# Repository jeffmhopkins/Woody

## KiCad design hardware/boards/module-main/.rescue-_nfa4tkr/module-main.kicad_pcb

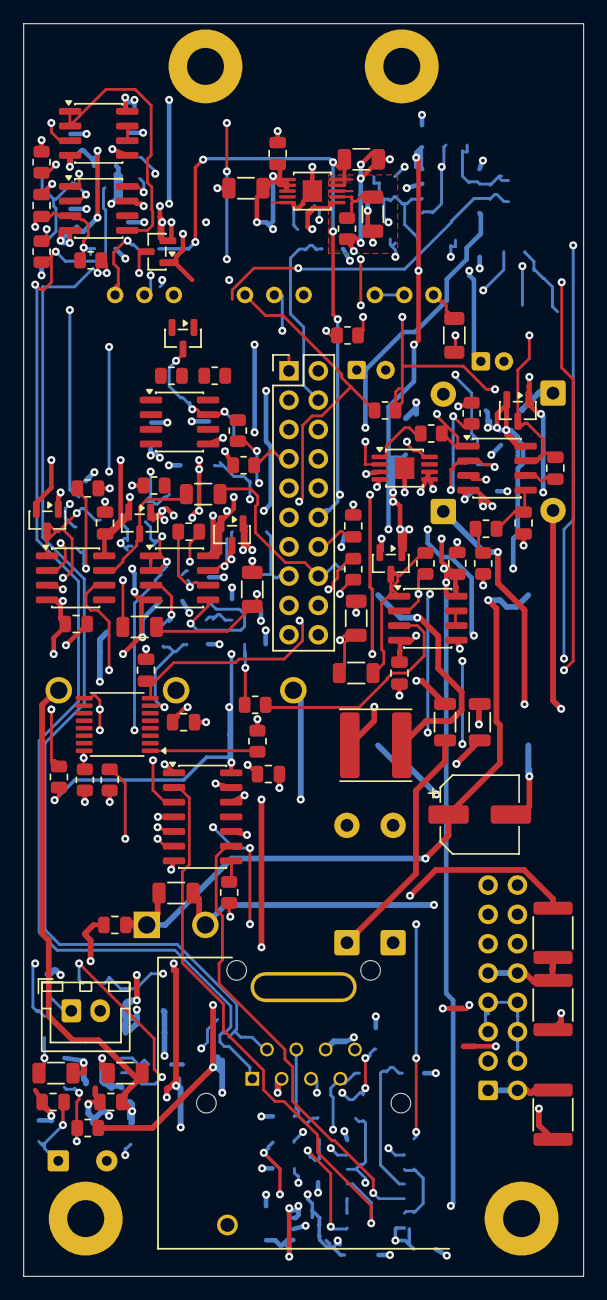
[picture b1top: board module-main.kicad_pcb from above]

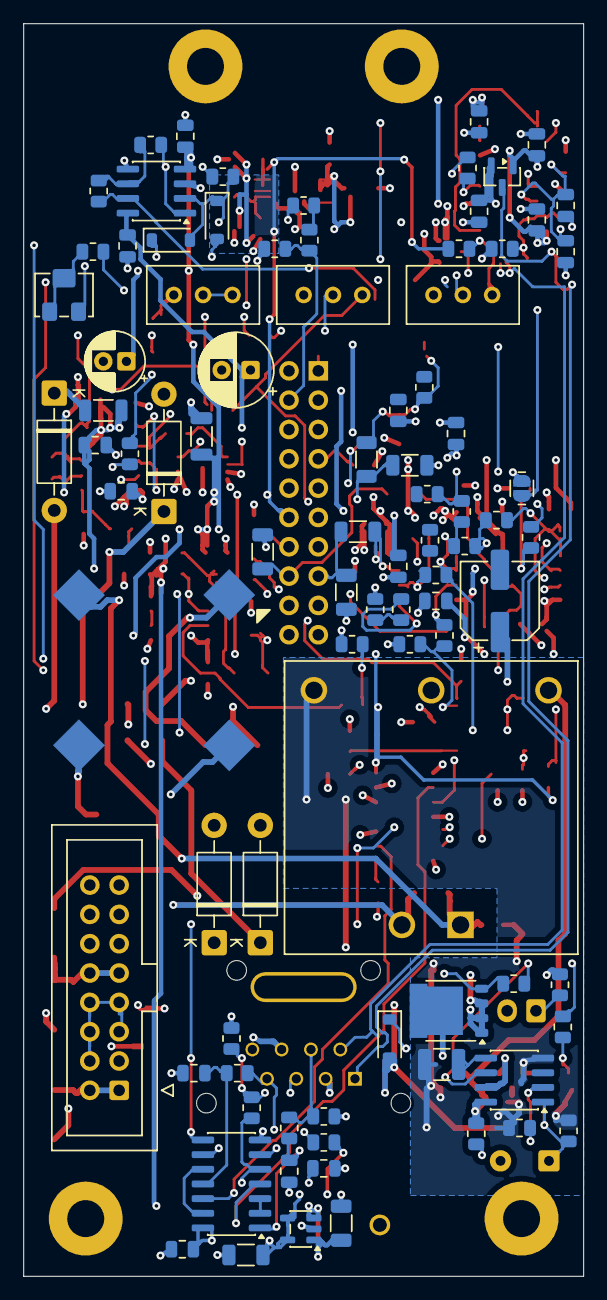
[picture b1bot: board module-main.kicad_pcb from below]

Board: 4 copper layers, 48.5 x 108.5 mm, 177 parts (89 on the bottom side), 113 nets.

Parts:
C1: 100uF; CP_Radial_D6.3mm_P2.50mm
C2: 100uF 50V; CP_Elec_6.3x7.7
C3: 47uF; CP_Radial_D5.0mm_P2.00mm
C5: 100nF; C_1206_3216Metric
C6, C51: 10uF; C_1206_3216Metric
C7, C10, C11, C12, C16, C17, C18, C19, C20, C21, C23, C24, C25, C26, C30, C31, C32, C33, C34, C35, C40, C43, C50: 100nF; C_0805_2012Metric
C8, C36, C37, C38, C39: 82nF; C_1206_3216Metric
C9: 10uF; C_1210_3225Metric
C13, C14: 1.5nF; C_0805_2012Metric
C15: 15nF; C_0805_2012Metric
C22: 330nF film; C_1206_3216Metric
C27, C29: 10nF; C_0805_2012Metric
C28: 2.2nF; C_0805_2012Metric
C41, C42: 4.7uF; C_1206_3216Metric
C44: 4.7uF 50V; C_1206_3216Metric
C45: 100uF 25V; CP_Elec_6.3x5.8
C46: 22nF; C_0805_2012Metric
C47, C48, C49: 47pF C0G; C_0805_2012Metric
D1, D2, D3, D15: 1N5817; D_DO-41_SOD81_P10.16mm_Horizontal
D4, D5, D6, D9, D10, D11, D12, D13: BAV99; SOT-23
D7, D8: 1N4448W; D_SOD-123
D14: 15V; D_SOD-123
F1, F3: MF-MSMF020/60-2; Fuse_1812_4532Metric
F2: MF-MSMF075/33X-2; Fuse_1812_4532Metric
FB1, FB2, FB3, FB4: 600R @ 100MHz; L_1206_3216Metric
H1: MECH-STANDOFF-MOD 1; MountingHole_3.2mm_M3_Pad
H2: MECH-STANDOFF-MOD 2; MountingHole_3.2mm_M3_Pad
H3: MECH-PANEL-STANDOFF-MOD 1; MountingHole_3.2mm_M3_Pad
H4: MECH-PANEL-STANDOFF-MOD 2; MountingHole_3.2mm_M3_Pad
J1: 2x8 2.54mm shrouded box header (16-pin); IDC-Header_2x08_P2.54mm_Vertical
J2: 2x10 2.54mm pin header; PinHeader_2x10_P2.54mm_Vertical
J3: Neutrik NE8FAV; Neutrik_NE8FAV_etherCON_Vertical
J4: JST B2B-XH-A; JST_XH_B2B-XH-A_1x02_P2.50mm_Vertical
JP1: 2-pad solder link; SolderJumper-2_P1.3mm_Open_RoundedPad1.0x1.5mm
L1: 22uH; L_Sunlord_SWPA6028S
L2: 1mH; L_CommonModeChoke_Bourns_PM3700
NT1, NT2, NT3: net tie; NetTie-2_SMD_Pad0.5mm
Q1: PSMN2R0-30YLE; LFPAK56
R1: 52.3k 0.1%; R_0805_2012Metric
R3: 50m 1% 1W; R_1206_3216Metric
R4: 10R 5%; R_0805_2012Metric
R5: 1k 5%; R_0805_2012Metric
R6: 35.7k 1%; R_0805_2012Metric
R7: 5.11k 1%; R_0805_2012Metric
R8, R10, R11, R13, R14, R15, R22, R28, R29, R30, R58, R59: 10k 1%; R_0805_2012Metric
R9: 0R strap; R_0805_2012Metric
R12, R33, R36, R38, R43, R48, R53: 100k 1%; R_0805_2012Metric
R16, R17, R39, R44, R49, R54, R65: 10k 0.1%; R_0805_2012Metric
R18, R19: 1M 1%; R_0805_2012Metric
R20: 42.2k 0.1%; R_0805_2012Metric
R21: 7.15k 1%; R_0805_2012Metric
R23: 21.0k 1%; R_0805_2012Metric
R24: 95.3k 1%; R_0805_2012Metric
R25: 40.2k 1%; R_0805_2012Metric
R26, R34, R41, R46, R51, R56: 1k 1%, >=500mW; R_1206_3216Metric
R27, R60: 20k 1%; R_0805_2012Metric
R31: 2.7k 1%; R_0805_2012Metric
R32, R35, R37, R42, R47, R52, R68, R69, R70: 1k 1%; R_0805_2012Metric
R40, R45, R50, R55: 30k 0.1%; R_0805_2012Metric
R57: 68k 1%; R_0805_2012Metric
R61: 100R 0.1%; R_0805_2012Metric
R62: 1k 0.1%; R_0805_2012Metric
R63: 22.1k 0.1%; R_0805_2012Metric
R64: 200R 0.1%; R_0805_2012Metric
R66: 42.2k 1%; R_0805_2012Metric
R71: 2k2 1%; R_0805_2012Metric
RN1: 10k; MSOP-8-1EP_3x3mm_P0.65mm_EP1.68x1.88mm
RV1, RV2: 10k multiturn cermet; Potentiometer_Bourns_3296W_Vertical
RV3: 200R multiturn cermet; Potentiometer_Bourns_3296W_Vertical
RV4: 10k 10% sealed SMD cermet; Potentiometer_Bourns_3224W_Vertical
SW1: NKK M2011SD4G01; SolderWire-0.25sqmm_1x02_P4.2mm_D0.65mm_OD1.7mm
U1: LT3042EMSE; MSOP-10-1EP_3x3mm_P0.5mm_EP1.68x1.88mm
U2: LT1641-1IS8; SOIC-8_3.9x4.9mm_P1.27mm
U3: DAC8568ICPW; TSSOP-16_4.4x5mm_P0.65mm
U4: 74AHCT125; SOIC-14_3.9x8.7mm_P1.27mm
U5, U7, U9, U10, U11, U12: OPA2197; SOIC-8_3.9x4.9mm_P1.27mm
U6: INA828IDR; SOIC-8_3.9x4.9mm_P1.27mm
U8: OPA2197IDR; SOIC-8_3.9x4.9mm_P1.27mm
U13: ADP7118AUJZ-5.0; TSOT-23-5
U14: RPA20-2412SAW; Converter_DCDC_RECOM_RPA20-RP20-xxxxSAW_THT
U15: 74AHCT14; SOIC-14_3.9x8.7mm_P1.27mm

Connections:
/AGND_SENSE: D4.3, J3.2, R16.1
/BREATH_INAMP_OUT: R27.1, R29.1, U6.6
/BREATH_JACK: C22.1, J2.11, R26.2
/BREATH_SENSE: D5.3, J3.1, R17.1
/BREATH_SHAPED: J2.1, R60.2, U8.7
/CS_MOD: J3.7, R12.1, R70.1
/DAC_AVDD: C6.1, C11.1, C12.1, J2.12, R8.1, R15.2, R66.1, U1.9, U1.10, U3.3, U4.14
/DAC_CH1: R32.1, R33.1, U3.4
/DAC_CH2: R37.1, R38.1, U3.13
/DAC_CH3: R42.1, R43.1, U3.5
/DAC_CH4: R47.1, R48.1, U3.12
/DAC_CH5: R52.1, R53.1, U3.6
/DAC_CH7: R35.1, R36.1, U3.7
/DIN: R14.1, U3.15, U4.6
/GAIN_FLOOR: J2.7, R21.1
/GAIN_WIPER: J2.3, U7.3
/MOD1_JACK: C36.1, J2.15, R41.2
/MOD2_JACK: C37.1, J2.17, R46.2
/MOD3_JACK: C38.1, J2.16, R51.2
/MOD4_JACK: C39.1, J2.20, R56.2
/MOSI: J3.5, R11.1, R69.1
/OFFSET_WIPER: J2.9, R23.1
/PITCH_JACK: C29.1, J2.14, R34.2, RV3.1
/RESP_V_IN_HALF: J2.4, R29.2, R30.1
/RESP_V_SHAPED: J2.8, R28.2, R59.1, U8.1
/RESP_WIPER: J2.6, R31.1
/SCLK: J3.4, R10.1, R68.1
/SCLK_DAC: R13.1, U3.16, U4.3
/SYNC: R15.1, U3.2, U4.8
/UMBILICAL_POS12: D14.2, J3.3, Q1.1, Q1.2, Q1.3, R6.1, R71.1
/VREFOUT: C43.1, R62.1, RV2.3, U3.8
/breath-output-stage/BREATH_OUT: D6.3, R25.2, R26.1, U7.7
/breath-output-stage/BUF_OUT: R22.1, U7.1, U7.2
/breath-output-stage/SUM_NODE: R22.2, R23.2, R24.2, R25.1, U7.6
/breath-receive-stage/GAIN_SET: R20.1, U6.1
/breath-receive-stage/GAIN_SET_B: R20.2, U6.8
/breath-receive-stage/IN_NEG: C14.1, C15.2, R17.2, R19.1, U6.2
/breath-receive-stage/IN_POS: C13.1, C15.1, R16.2, R18.1, U6.3
/breath-receive-stage/REF_DRIVE: U5.1, U5.2, U6.5
/breath-receive-stage/SPARE_B_OUT: U5.6, U5.7
/breath-receive-stage/TRIM_WIPER: RV1.2, U5.3
/breath-receive-stage/ZERO_TOP: R66.2, RV1.3
/breath-response-shaper/DIODE_BRANCH: D7.1, D8.2, RV4.3
/breath-response-shaper/RESP_TRIM: R31.2, RV4.1, RV4.2
/breath-response-shaper/RESTORE_SUM: R59.2, R60.1, U8.6
/breath-response-shaper/VIRTUAL_GND: D7.2, D8.1, R27.2, R28.1, U8.2
/dac8568/CLR: JP1.1, R8.2, U3.9
/dac8568/LDAC: R9.1, U3.1
/digital-and-supervision/CS_BUF: U4.9, U15.12
/digital-and-supervision/CS_N: U15.10, U15.13
/digital-and-supervision/CS_RC: C49.1, R70.2, U15.11
/digital-and-supervision/MOSI_BUF: U4.5, U15.8
/digital-and-supervision/MOSI_N: U15.6, U15.9
/digital-and-supervision/MOSI_RC: C48.1, R69.2, U15.5
/digital-and-supervision/SCLK_BUF: U4.2, U15.4
/digital-and-supervision/SCLK_N: U15.2, U15.3
/digital-and-supervision/SCLK_RC: C47.1, R68.2, U15.1
/mod-channels/MINUS_1: R39.2, R40.1, U10.6
/mod-channels/MINUS_2: R44.2, R45.1, U11.2
/mod-channels/MINUS_3: R49.2, R50.1, U11.6
/mod-channels/MINUS_4: R54.2, R55.1, U12.2
/mod-channels/OUT_1: D10.3, R40.2, R41.1, U10.7
/mod-channels/OUT_2: D11.3, R45.2, R46.1, U11.1
/mod-channels/OUT_3: D12.3, R50.2, R51.1, U11.7
/mod-channels/OUT_4: D13.3, R55.2, R56.1, U12.1
/mod-channels/PLUS_1: R37.2, U10.5
/mod-channels/PLUS_2: R42.2, U11.3
/mod-channels/PLUS_3: R47.2, U11.5
/mod-channels/PLUS_4: R52.2, U12.3
/mod-channels/REF_PLUS: R35.2, U10.3
/mod-channels/SPARE_C_OUT: U12.6, U12.7
/mod-channels/VREF_MOD: R39.1, R44.1, R49.1, R54.1, U10.1, U10.2
/panel-led/LED_ANODE: J4.1, R71.2
/pitch-stage/AMP_OUT: C28.1, D9.3, R34.1, U9.7
/pitch-stage/GAIN_TRIM_MID: RN1.7, RV3.2, RV3.3
/pitch-stage/MINUS_NODE: C28.2, RN1.2, RN1.8, U9.6
/pitch-stage/PLUS_NODE: C27.1, R32.2, U9.5
/pitch-stage/R1_BOTTOM: R61.1, RN1.1
/pitch-stage/TRIM_WIPER: R63.1, RV2.2
/pitch-stage/VREF_BUFFERED: R61.2, R64.1, U9.1
/pitch-stage/VREF_FB: R64.2, R65.1, U9.2
/pitch-stage/VREF_SUM: R62.2, R63.2, U9.3
/power-entry/BUS_GND: J1.3, J1.4, J1.5, J1.6, J1.7, J1.8, NT1.2, NT2.2
/power-entry/BUS_NEG12_RAW: D15.1, F3.1, J1.1, J1.2
/power-entry/BUS_POS12_RAW: F1.1, F2.1, J1.9, J1.10
/power-entry/DAC_REG_SET: C5.1, R1.1, U1.7
/power-entry/ISO_FB2: FB2.2, L1.1
/power-entry/ISO_FILT_NEG: FB4.2, L2.4
/power-entry/ISO_FILT_POS: L1.2, L2.1
/power-entry/ISO_VIN_NEG: C2.2, C44.2, L2.3, U14.2
/power-entry/ISO_VIN_POS: C2.1, C44.1, C46.1, L2.2, U14.1
/power-entry/NEG12_D4: D15.2, FB4.1
/power-entry/NEG12_FB: D3.2, FB3.1
/power-entry/NEG12_PTC3: D3.1, F3.2
/power-entry/POS12_D1: D1.1, FB1.1
/power-entry/POS12_D2: D2.1, FB2.1
/power-entry/POS12_PTC1: D1.2, F1.2
/power-entry/POS12_PTC2: D2.2, F2.2
/umbilical-load-switch/FB: R6.2, R7.1, U2.2
/umbilical-load-switch/GATE_COMP_MID: C8.1, R5.2
/umbilical-load-switch/GATE_DRIVE: R4.1, R5.1, U2.6
/umbilical-load-switch/GATE_NODE: D14.1, Q1.4, R4.2
/umbilical-load-switch/ON: C40.1, R58.1, SW1.1, U2.1
/umbilical-load-switch/ON_SW: R57.2, SW1.2
/umbilical-load-switch/SENSE_NODE: Q1.5, R3.2, U2.7
/umbilical-load-switch/TIMER: C9.1, U2.5
AGND_MOD: C1.2, C3.2, C5.2, C6.2, C7.2, C11.2, C13.2, C14.2, C16.2, C17.2, C18.2, C19.2, C20.2, C21.2, C22.2, C23.2, C24.2, C25.2, C26.2, C27.2, C29.2, C30.2, C31.2, C32.2, C33.2, C34.2, C35.2, C36.2, C37.2, C38.2, C39.2, C43.2, C51.2, J2.2, J2.5, J2.10, J2.13, J2.18, J4.2, JP1.2, NT1.1, R1.2, R9.2, R18.2, R19.2, R21.2, R30.2, R33.2, R36.2, R38.2, R43.2, R48.2, R53.2, R65.2, RN1.3, RN1.4, RN1.5, RN1.6, RN1.9, RV1.1, RV2.1, U1.5, U1.8, U1.11, U3.14, U5.5, U7.5, U8.3, U8.5, U12.5
DIG_GND: C12.2, C41.2, C42.2, C47.2, C48.2, C49.2, C50.2, J3.8, NT2.1, NT3.2, R10.2, R11.2, R13.2, R14.2, U4.1, U4.4, U4.7, U4.10, U4.12, U4.13, U13.2, U15.7
ISO_POS12: C10.1, C45.1, R3.1, R57.1, U2.8, U14.6
LOGIC_5V: C42.1, C50.1, R12.2, U13.4, U13.5, U15.14
MODULE_ANALOG_NEG12: C3.1, C17.1, C19.1, C21.1, C24.1, C26.1, C31.1, C33.1, C35.1, D4.1, D5.1, D6.1, D9.1, D10.1, D11.1, D12.1, D13.1, FB3.2, R24.1, U5.4, U6.4, U7.4, U8.4, U9.4, U10.4, U11.4, U12.4
MODULE_ANALOG_POS12: C1.1, C7.1, C16.1, C18.1, C20.1, C23.1, C25.1, C30.1, C32.1, C34.1, C41.1, C51.1, D4.2, D5.2, D6.2, D9.2, D10.2, D11.2, D12.2, D13.2, FB1.2, U1.1, U1.2, U1.3, U1.6, U5.8, U6.7, U7.8, U8.8, U9.8, U10.8, U11.8, U12.8, U13.1, U13.3
PWR_GND: C8.2, C9.2, C10.2, C40.2, C45.2, C46.2, J3.6, NT3.1, R7.2, R58.2, U2.4, U14.4
